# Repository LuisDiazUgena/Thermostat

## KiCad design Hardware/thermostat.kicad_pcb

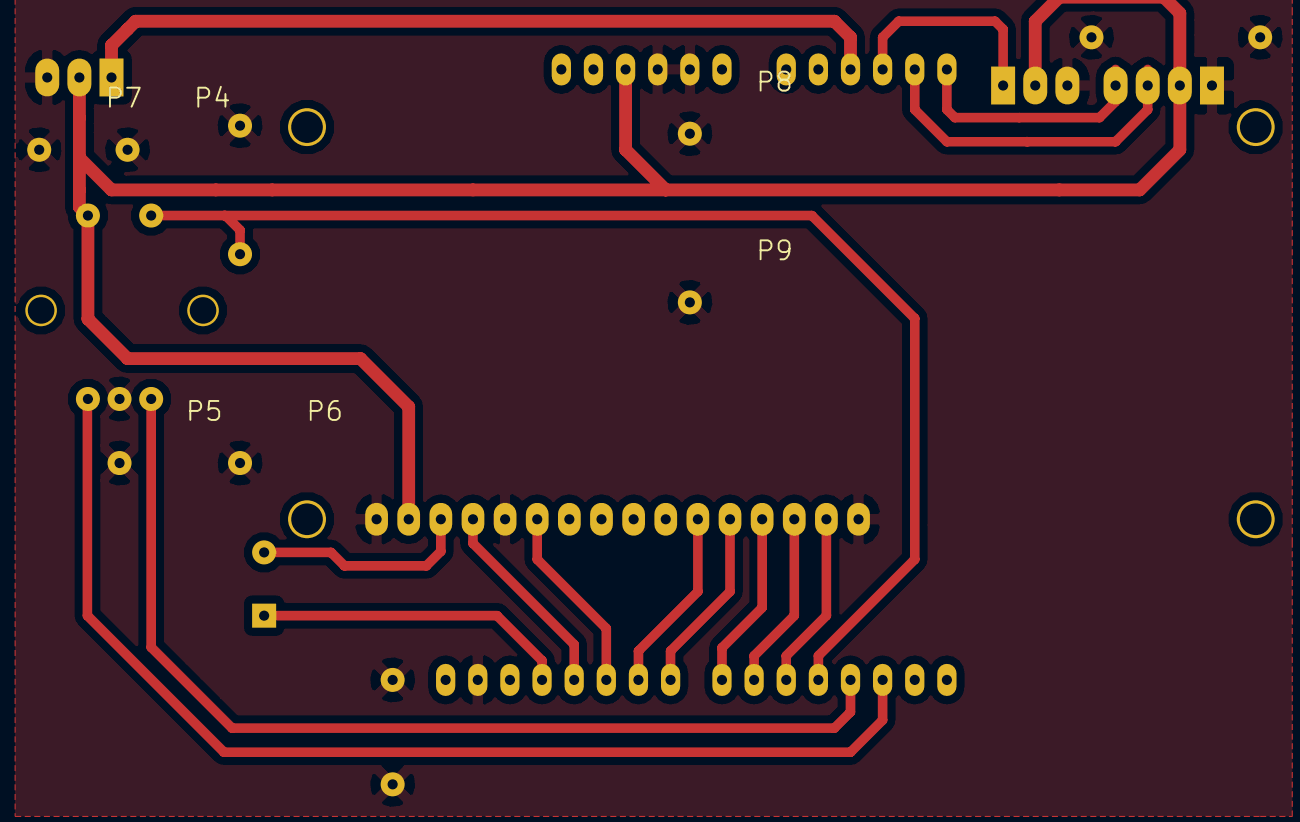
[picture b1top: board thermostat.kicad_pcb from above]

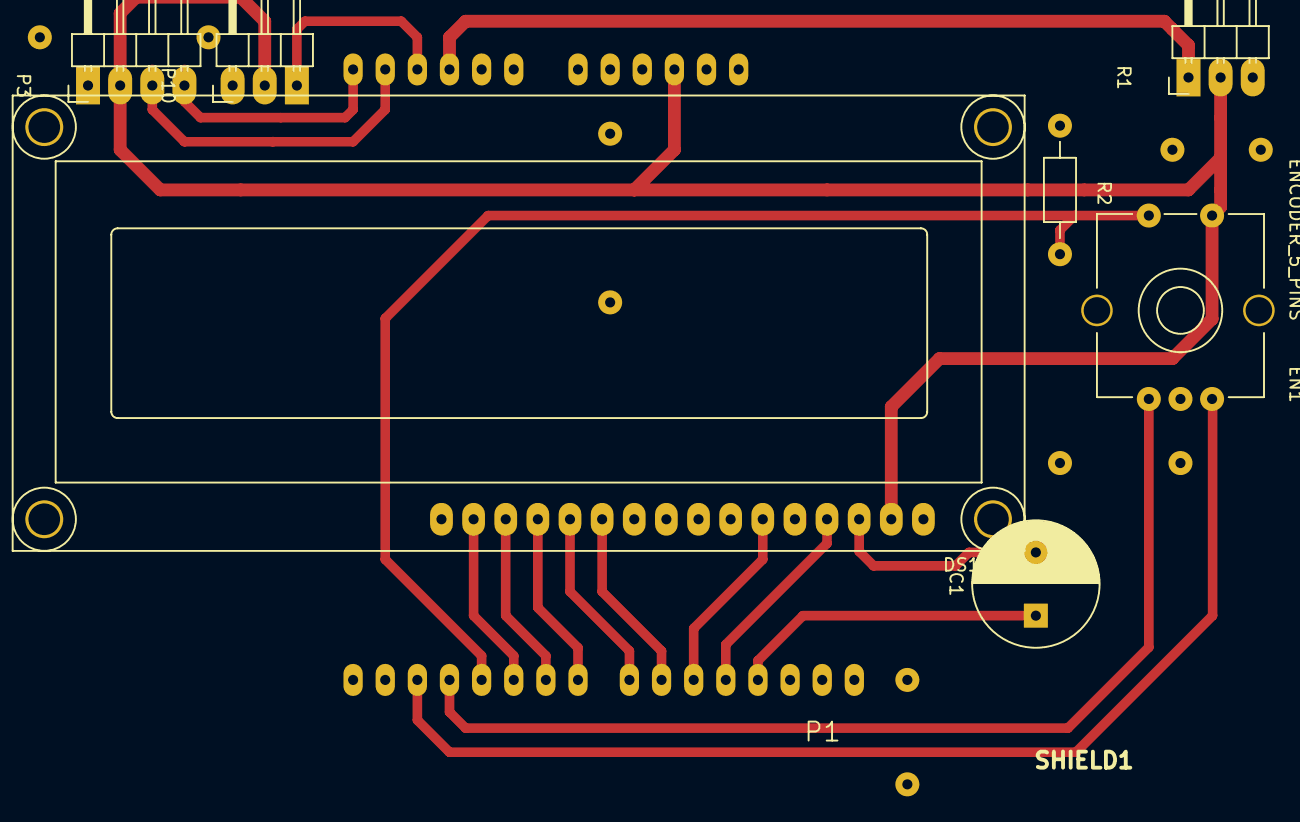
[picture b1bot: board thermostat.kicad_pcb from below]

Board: 2 copper layers, 18 parts (10 on the bottom side), 18 nets.

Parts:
C1: 100uF; C_Radial_D10_L13_P5
DS1: LCD16X2; WC1602A
EN1: ENCODER_5_PINS
P1, P2, P4, P5, P6, P7, P8, P9, P11, P12: CONN_01X01; header1x01
P3: CONN_01X04 (T&H); Pin_Header_Angled_1x04
P10: CONN_01X03; Pin_Header_Angled_1x03
R1: relay_module; Pin_Header_Angled_1x03
R2: 10K; Resistor_Horizontal_RM10mm
SHIELD1: ARDUINO_SHIELD; ARDUINO_SHIELD_2

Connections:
BKL: DS1.15, SHIELD1.5
BTN: EN1.4, R2.2, SHIELD1.4
D4: DS1.11, SHIELD1.9
D5: DS1.12, SHIELD1.8
D6: DS1.13, SHIELD1.7
D7: DS1.14, SHIELD1.6
E: DS1.6, SHIELD1.10
GND: DS1.1, DS1.5, DS1.16, EN1.2, P1.1, P2.1, P3.1, P4.1, P5.1, P6.1, P7.1, P8.1, P9.1, P10.1, P11.1, P12.1, R1.3, R2.1, SHIELD1.GND1, SHIELD1.GND2, SHIELD1.GND3
unnamed: C1.2, DS1.3
unnamed: EN1.1, SHIELD1.3
unnamed: EN1.3, SHIELD1.2
RELAY: R1.1, SHIELD1.AD2
RS: DS1.4, SHIELD1.11
SCL: P3.4, SHIELD1.AD5
SDA: P3.3, SHIELD1.AD4
SGN: P10.3, SHIELD1.AD3
V0: C1.1, SHIELD1.12
VCC: DS1.2, EN1.5, P3.2, P10.2, R1.2, SHIELD1.5V

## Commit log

2015-08-19 Added LCD
2015-08-19 Added HTS221 (T&H), encoder and relay support (bassed in temp difference)
2015-08-19 Added encoder
2015-08-19 Added value to pasive parts
2015-08-19 Increase code efficiency
2015-08-19 Removed wrong libraries
2015-08-20 Added temperature selection routine
2015-08-20 Added updateTime routine to sketch
2015-08-20 added support for menus, show stats and improved code
2015-08-21 Added save/load from eeprom
2015-08-21 Added delete EEPROM values function
2015-08-25 Added headers to improve ground connectivity and added relay and temp&hum headers
2015-08-25 Added 3 pin header for analog device, decrease pcb size
2015-08-25 Added gerbers
2015-08-25 improved pads
